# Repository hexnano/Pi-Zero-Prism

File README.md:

# Pi-Zero-Prism
Stuff related to Pi Zero Prism

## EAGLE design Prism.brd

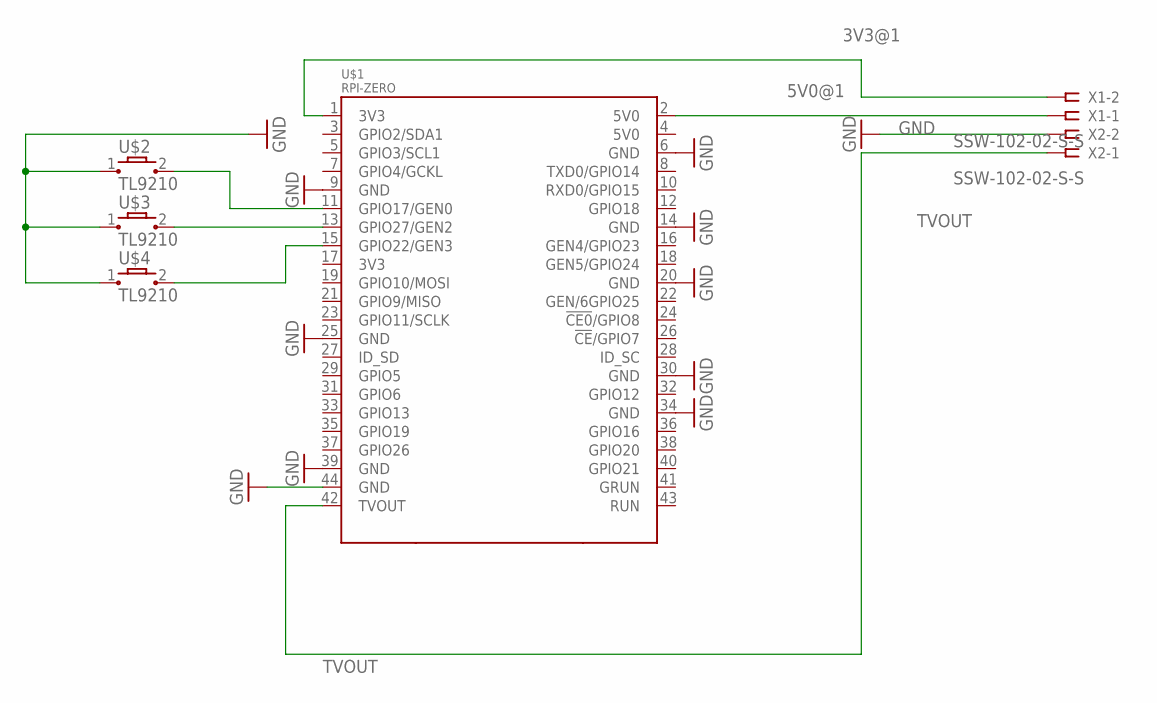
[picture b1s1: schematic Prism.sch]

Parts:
U$1: RPI-ZERO; RASPBERRYPI_BASTELSTUBE_V13_RASPI_BOARD_B+_FULL
U$2, U$3, U$4: TL9210
X1, X2: SSW-102-02-S-S

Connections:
3V3@1: U$1.1 (3V3), X1.2
5V0@1: U$1.2 (5V0), X1.1
GND: U$1.6 (GND), U$1.9 (GND), U$1.14 (GND), U$1.20 (GND), U$1.25 (GND), U$1.30 (GND), U$1.34 (GND), U$1.39 (GND), U$1.44 (GND), U$2.1, U$3.1, U$4.1, X2.2
unnamed: U$1.11 (GPIO17/GEN0), U$2.2
unnamed: U$1.13 (GPIO27/GEN2), U$3.2
unnamed: U$1.15 (GPIO22/GEN3), U$4.2
TVOUT: U$1.42 (TVOUT), X2.1

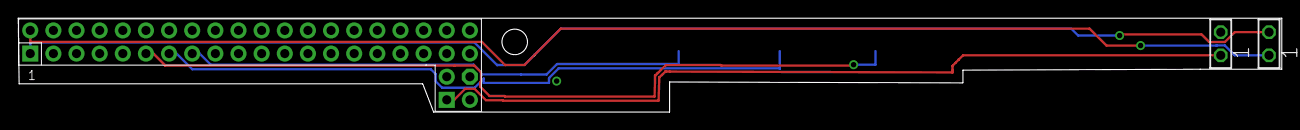
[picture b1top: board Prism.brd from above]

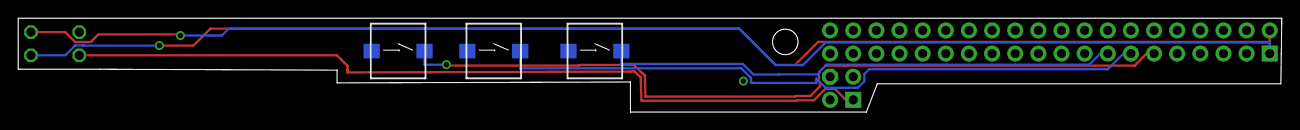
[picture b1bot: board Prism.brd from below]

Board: 2 copper layers, 138.7 x 10.3 mm, 6 parts (3 on the bottom side), 7 nets.
